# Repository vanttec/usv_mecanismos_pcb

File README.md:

# usv_mecanismos_pcb
PCB de Mecanismos
* STM32L431RTC
* Puente H (2) (6A maximo consumo, diseñar a 12A o 9A supongo)
* Drivers p/steppers (2)
* Conectores de seguridad (Molex?)
* CAN (MAX330 transcievers?) (1)
* Level Shifters (3.3V a 5V) (no se cuantos)

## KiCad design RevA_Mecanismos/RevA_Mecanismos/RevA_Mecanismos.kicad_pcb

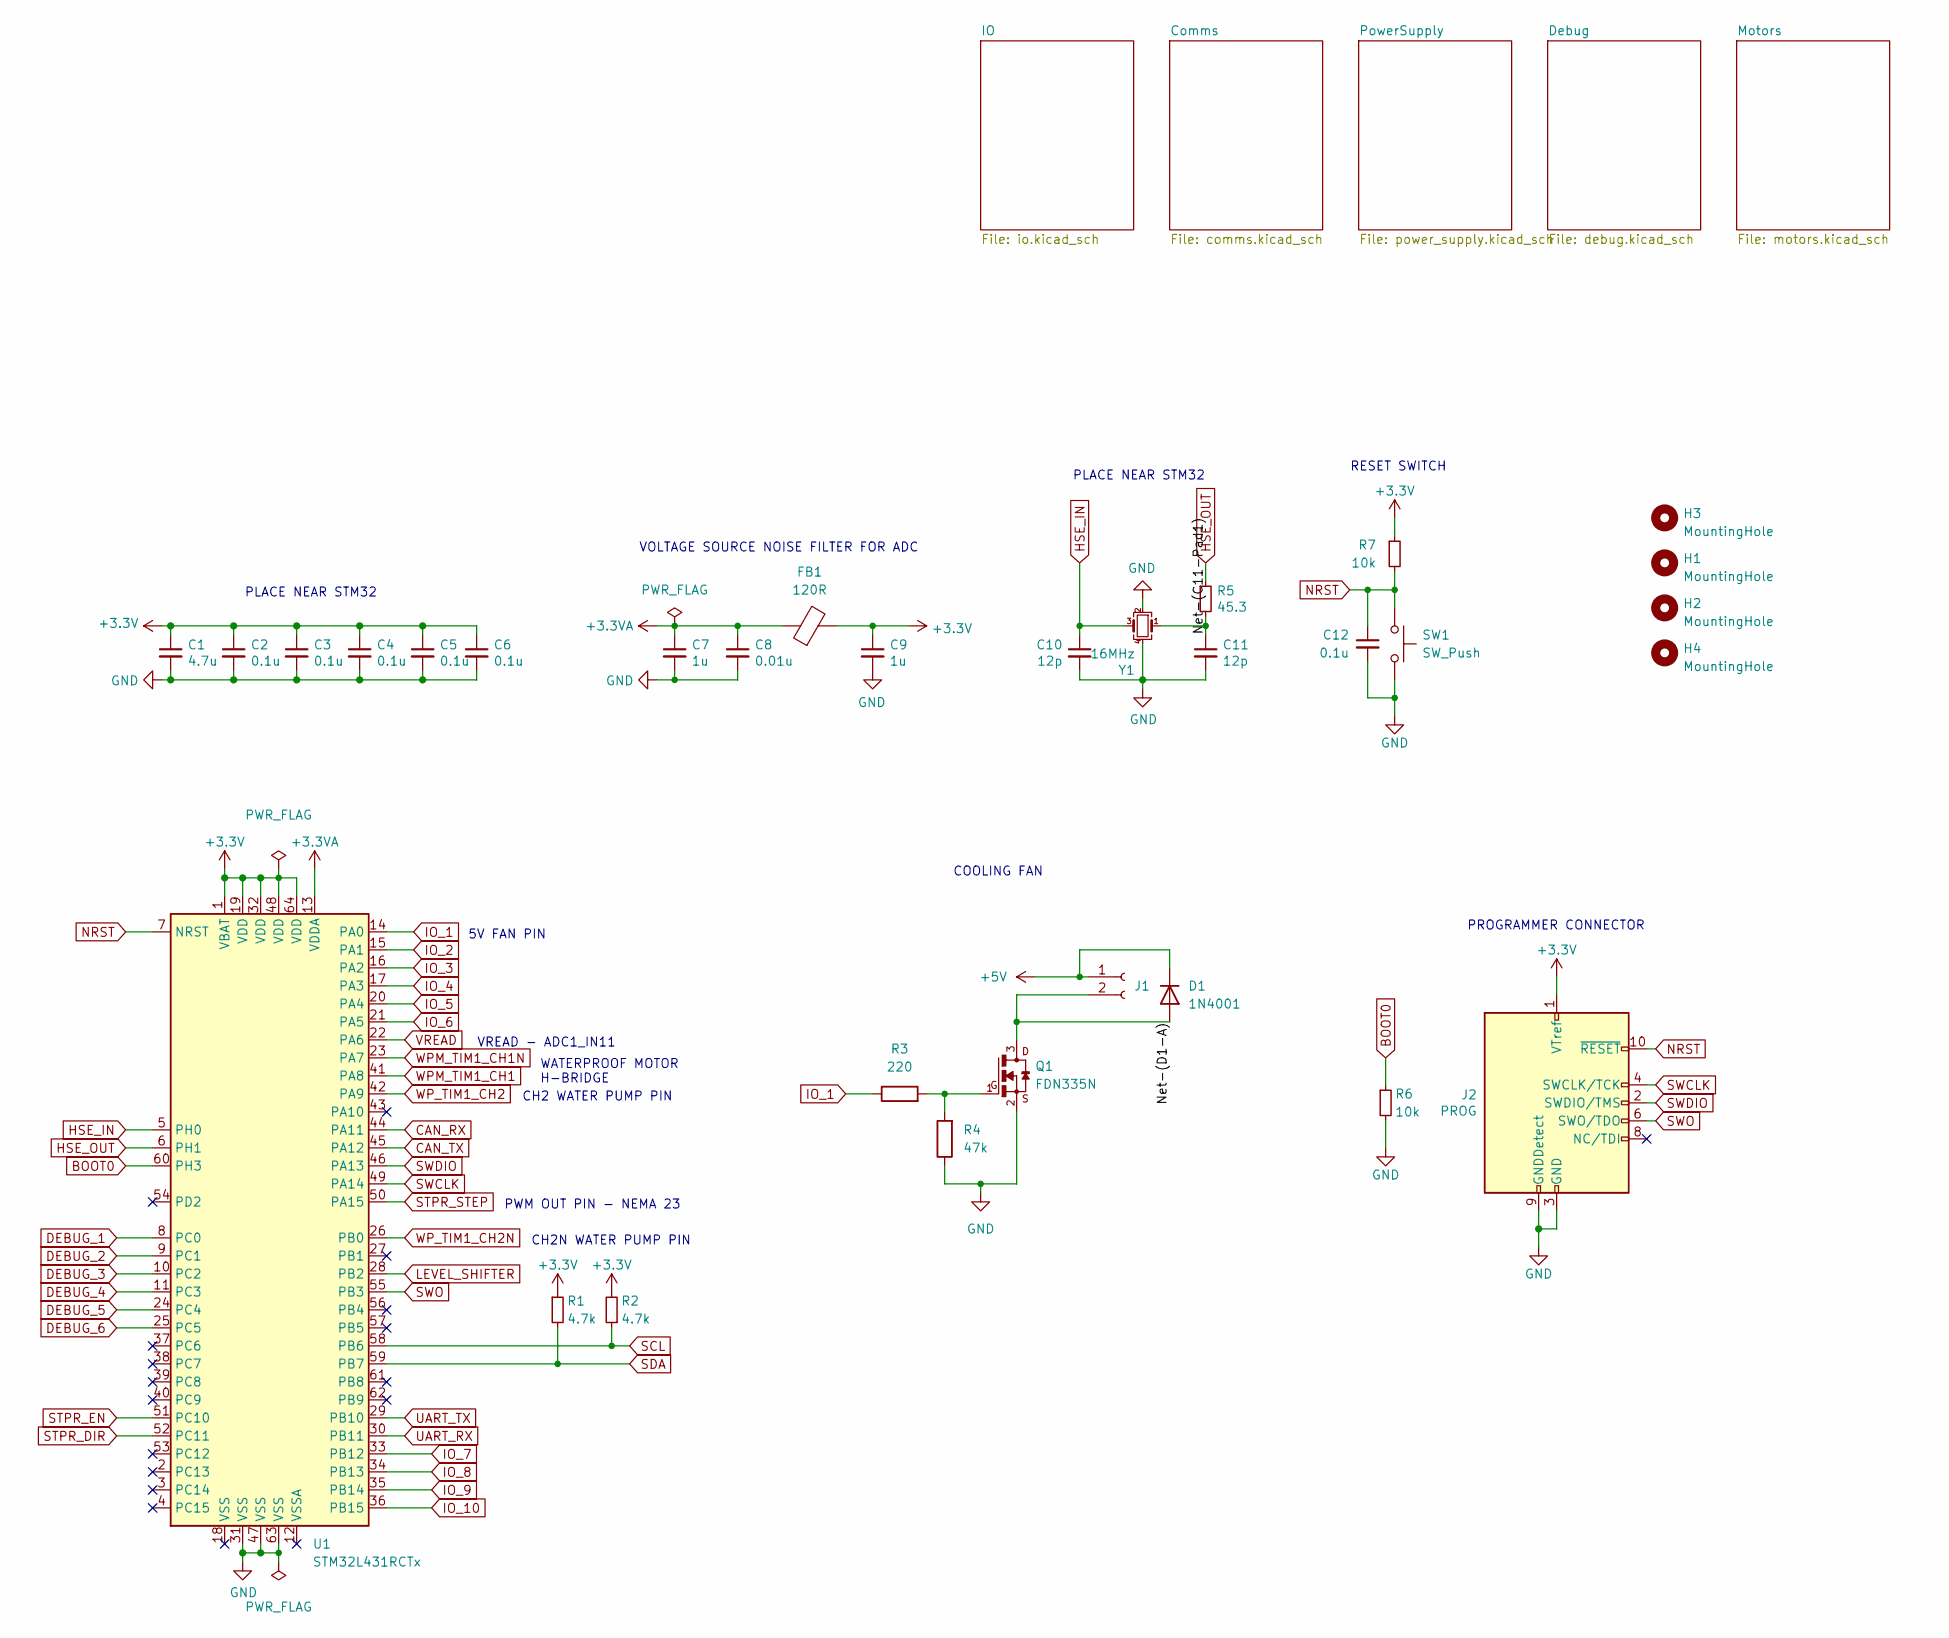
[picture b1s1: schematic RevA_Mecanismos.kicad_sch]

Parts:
C1: 4.7u; C_0603_1608Metric; PartNumber C0603C104K4RECTU; LCSC C165952
C2, C3, C4, C5, C6, C12: 0.1u; C_0603_1608Metric; PartNumber C0603C104K4RECTU; LCSC C165952
C7, C9: 1u; C_0603_1608Metric; PartNumber C0603C104K4RECTU; LCSC C165952
C8: 0.01u; C_0603_1608Metric; PartNumber C0603C104K4RECTU; LCSC C165952
C10, C11: 12p; C_0603_1608Metric; PartNumber C0603C120K5HACTU; LCSC C38523
D1: 1N4001; D_DO-41_SOD81_P10.16mm_Horizontal
FB1: 120R; L_0603_1608Metric
H1, H2, H3, H4: MountingHole; MountingHole_2.7mm_M2.5_DIN965_Pad
J1: Conn_01x02_Pin; PinHeader_1x02_P2.54mm_Vertical
J2: PROG; PinHeader_2x05_P1.27mm_Vertical; PartNumber 62201021121
Q1: FDN335N; SSOT-3; DigiKey_Part_Number FDN335NTR-ND
R1, R2: 4.7k; R_0603_1608Metric
R3: 220; R_0603_1608Metric
R4: 47k; R_0603_1608Metric
R5: 45.3; R_0603_1608Metric; PartNumber CRCW060347R0JNEAC; LCSC C23182
R6: 10k; R_0603_1608Metric
R7: 10k; R_0603_1608Metric; PartNumber CRCW06030000Z0EBC; LCSC C101250
SW1: SW_Push; SW_SPST_TL3305A
U1: STM32L431RCTx; LQFP-64_10x10mm_P0.5mm
Y1: 16MHz; Crystal_SMD_3225-4Pin_3.2x2.5mm; PartNumber ECS-160-12-33-AGN-TR; LCSC C13738

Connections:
+3.3V: C1.1, C2.1, C3.1, C4.1, C5.1, C6.1, C9.1, FB1.2, J2.1 (VTref), R1.1, R2.2, R7.1, U1.1 (VBAT), U1.19 (VDD), U1.32 (VDD), U1.48 (VDD), U1.64 (VDD); also elsewhere on the board
+3.3VA: C7.1, C8.1, FB1.1, U1.13 (VDDA)
+5V: D1.1 (K), J1.1; also elsewhere on the board
/Net-(C11-Pad1): C11.1, R5.2, Y1.1
/Net-(D1-A): D1.2 (A), J1.2, Q1.3
BOOT0: R6.1, U1.60 (PH3)
CAN_RX: U1.44 (PA11); also elsewhere on the board
CAN_TX: U1.45 (PA12); also elsewhere on the board
DEBUG_1: U1.8 (PC0); also elsewhere on the board
DEBUG_2: U1.9 (PC1); also elsewhere on the board
DEBUG_3: U1.10 (PC2); also elsewhere on the board
DEBUG_4: U1.11 (PC3); also elsewhere on the board
DEBUG_5: U1.24 (PC4); also elsewhere on the board
DEBUG_6: U1.25 (PC5); also elsewhere on the board
GND: C1.2, C2.2, C3.2, C4.2, C5.2, C6.2, C7.2, C8.2, C9.2, C10.2, C11.2, C12.2, J2.3 (GND), J2.5 (GND), J2.9 (GNDDetect), Q1.2, R4.1, R6.2, SW1.2, U1.31 (VSS), U1.47 (VSS), U1.63 (VSS), Y1.2, Y1.4; also elsewhere on the board
HSE_IN: C10.1, U1.5 (PH0), Y1.3
HSE_OUT: R5.1, U1.6 (PH1)
IO_1: R3.1, U1.14 (PA0)
IO_2: U1.15 (PA1); also elsewhere on the board
IO_3: U1.16 (PA2); also elsewhere on the board
IO_4: U1.17 (PA3); also elsewhere on the board
IO_5: U1.20 (PA4); also elsewhere on the board
IO_6: U1.21 (PA5); also elsewhere on the board
IO_7: U1.33 (PB12); also elsewhere on the board
IO_8: U1.34 (PB13); also elsewhere on the board
IO_9: U1.35 (PB14); also elsewhere on the board
IO_10: U1.36 (PB15); also elsewhere on the board
LEVEL_SHIFTER: U1.28 (PB2); also elsewhere on the board
NRST: C12.1, J2.10 (~RESET), R7.2, SW1.1, U1.7 (NRST)
unnamed: Q1.1, R3.2, R4.2
SCL: R2.1, U1.58 (PB6); also elsewhere on the board
SDA: R1.2, U1.59 (PB7); also elsewhere on the board
STPR_DIR: U1.52 (PC11); also elsewhere on the board
STPR_EN: U1.51 (PC10); also elsewhere on the board
STPR_STEP: U1.50 (PA15); also elsewhere on the board
SWCLK: J2.4 (SWCLK/TCK), U1.49 (PA14)
SWDIO: J2.2 (SWDIO/TMS), U1.46 (PA13)
SWO: J2.6 (SWO/TDO), U1.55 (PB3)
UART_RX: U1.30 (PB11); also elsewhere on the board
UART_TX: U1.29 (PB10); also elsewhere on the board
VREAD: U1.22 (PA6); also elsewhere on the board
WPM_TIM1_CH1: U1.41 (PA8); also elsewhere on the board
WPM_TIM1_CH1N: U1.23 (PA7); also elsewhere on the board
WP_TIM1_CH2: U1.42 (PA9); also elsewhere on the board
WP_TIM1_CH2N: U1.26 (PB0); also elsewhere on the board

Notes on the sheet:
5V FAN PIN
RESET SWITCH
VOLTAGE SOURCE NOISE FILTER FOR ADC
CH2N WATER PUMP PIN
VREAD - ADC1_IN11
COOLING FAN
PLACE NEAR STM32
PROGRAMMER CONNECTOR
PWM OUT PIN - NEMA 23
CH2 WATER PUMP PIN
WATERPROOF MOTOR H-BRIDGE

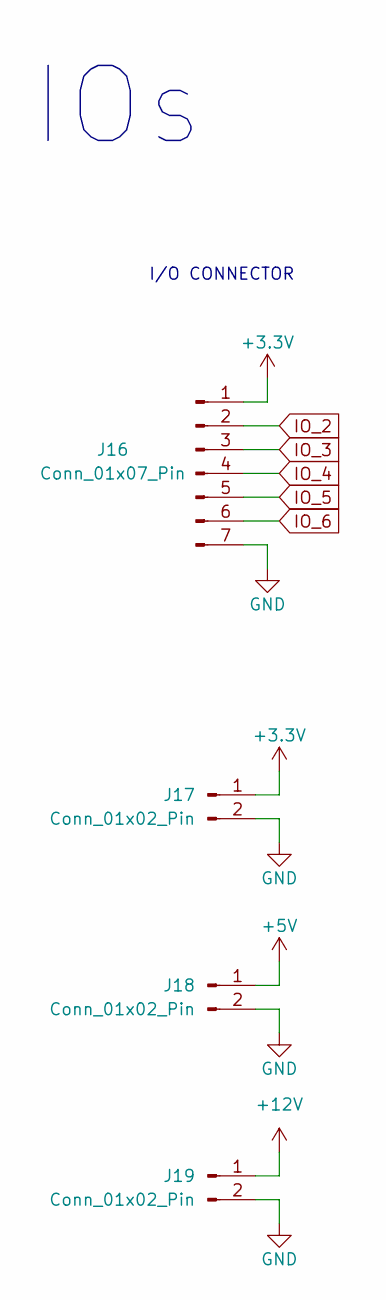
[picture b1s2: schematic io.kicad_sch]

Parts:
J16: Conn_01x07_Pin; PinHeader_1x02_P2.54mm_Vertical
J17: Conn_01x02_Pin; PinHeader_1x02_P2.54mm_Vertical
J18, J19: Conn_01x02_Pin; PinHeader_1x04_P2.54mm_Vertical

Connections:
+3.3V: J16.1, J17.1; also elsewhere on the board
+5V: J18.1; also elsewhere on the board
+12V: J19.1; also elsewhere on the board
GND: J16.7, J17.2, J18.2, J19.2; also elsewhere on the board
IO_2: J16.2; also elsewhere on the board
IO_3: J16.3; also elsewhere on the board
IO_4: J16.4; also elsewhere on the board
IO_5: J16.5; also elsewhere on the board
IO_6: J16.6; also elsewhere on the board

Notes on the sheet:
I/O CONNECTOR
IOs

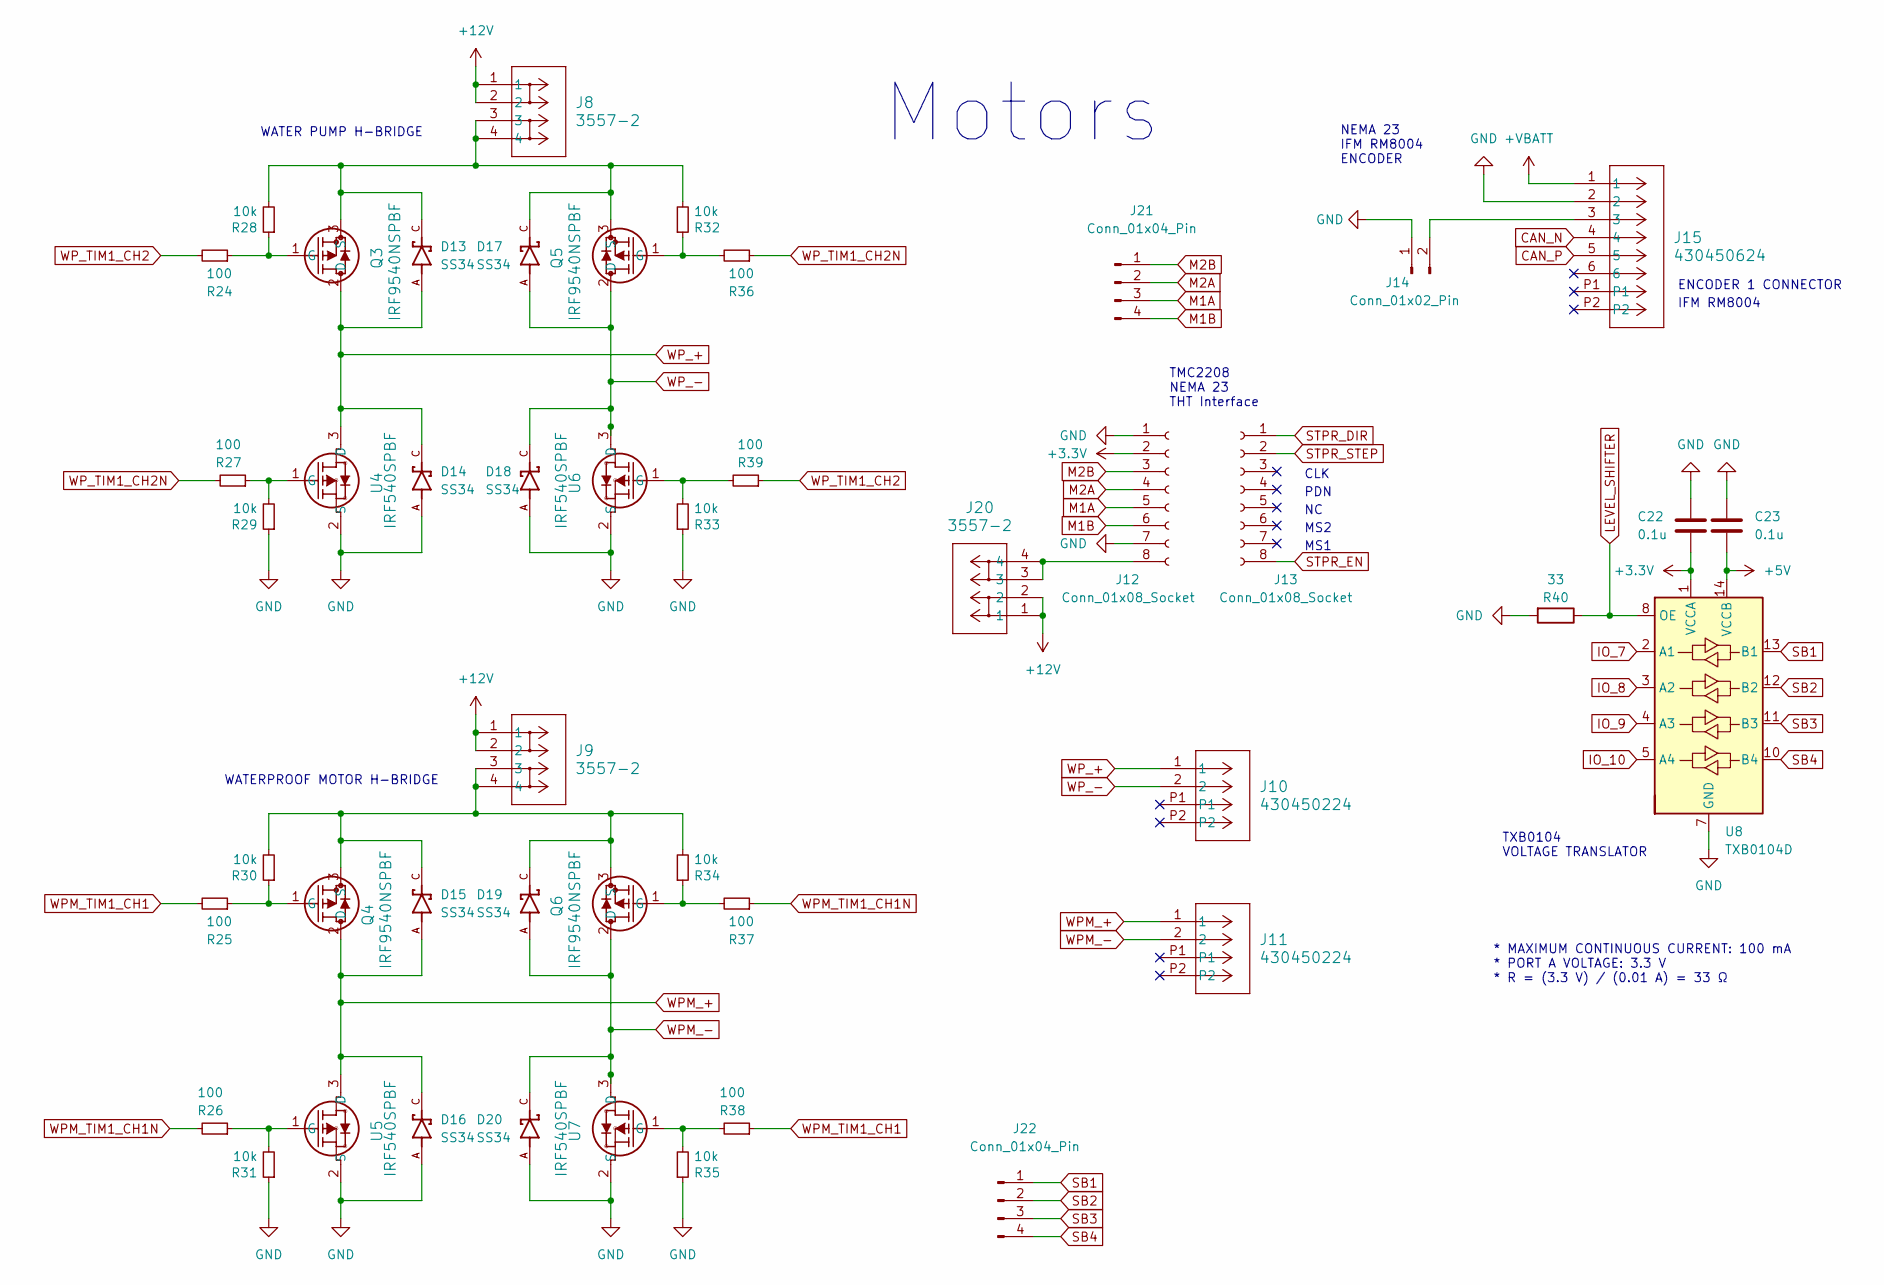
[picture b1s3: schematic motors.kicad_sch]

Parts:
C22, C23: 0.1u; C_0603_1608Metric
D13, D14, D15, D16, D17, D18, D20: SS34; DIOM7959X265N; PARTREV 31 Aug 2016
D19: SS34; PARTREV 31 Aug 2016
J8, J9: 3557-2; CONN_3557-2_KEY
J10, J11: 430450224; CON_430450224_MOL
J12: Conn_01x08_Socket; PinSocket_1x08_P2.54mm_Vertical
J13: Conn_01x08_Socket; CON_430450624_MOL
J14: Conn_01x02_Pin; PinHeader_1x07_P2.54mm_Vertical
J15: 430450624; PinHeader_1x02_P2.54mm_Vertical
J20: 3557-2; TerminalBlock_Altech_AK300-2_P5.00mm
J21, J22: Conn_01x04_Pin; PinHeader_1x04_P2.54mm_Vertical
Q3, Q4, Q5, Q6: IRF9540NSPBF; PMOSGDS_D2PAK_INF
R24, R25, R26, R27, R36, R37, R38, R39: 100; R_0603_1608Metric; PartNumber RGT1608P-821-B-T5; LCSC C101202
R28, R29, R30, R31, R32, R33, R34, R35: 10k; R_0603_1608Metric; PartNumber RGT1608P-821-B-T5; LCSC C101202
R40: 33; R_0603_1608Metric
U4, U5, U6, U7: IRF540SPBF; D2PAK_VIS
U8: TXB0104D; SOIC-14_3.9x8.7mm_P1.27mm

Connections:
+3.3V: C22.2, J12.2, U8.1 (VCCA); also elsewhere on the board
+5V: C23.2, U8.14 (VCCB); also elsewhere on the board
+12V: J8.1, J8.2, J9.1, J9.2, J20.1, J20.2; also elsewhere on the board
+VMOT: J15.1; also elsewhere on the board
CAN_N: J15.4; also elsewhere on the board
CAN_P: J15.5; also elsewhere on the board
GND: C22.1, C23.1, D14.A, D16.A, D18.A, D20.A, J12.1, J12.7, J14.1, J15.2, R29.1, R31.1, R33.1, R35.1, R40.2, U4.2 (S), U5.2 (S), U6.2 (S), U7.2 (S), U8.7 (GND); also elsewhere on the board
IO_7: U8.2 (A1); also elsewhere on the board
IO_8: U8.3 (A2); also elsewhere on the board
IO_9: U8.4 (A3); also elsewhere on the board
IO_10: U8.5 (A4); also elsewhere on the board
LEVEL_SHIFTER: R40.1, U8.8 (OE); also elsewhere on the board
M1A: J12.5, J21.3
M1B: J12.6, J21.4
M2A: J12.4, J21.2
M2B: J12.3, J21.1
unnamed: J12.8, J20.3, J20.4
unnamed: J14.2, J15.3
unnamed: Q3.1 (G), R24.1, R28.1
unnamed: D13.C, D17.C, J8.3, J8.4, Q3.3 (S), Q5.3 (S), R28.2, R32.2
unnamed: Q4.1 (G), R25.1, R30.1
unnamed: D15.C, D19.C, J9.3, J9.4, Q4.3 (S), Q6.3 (S), R30.2, R34.2
unnamed: Q5.1 (G), R32.1, R36.2
unnamed: Q6.1 (G), R34.1, R37.2
unnamed: R27.1, R29.2, U4.1 (G)
unnamed: R26.1, R31.2, U5.1 (G)
unnamed: R33.2, R39.2, U6.1 (G)
unnamed: R35.2, R38.2, U7.1 (G)
SB1: J22.1, U8.13 (B1)
SB2: J22.2, U8.12 (B2)
SB3: J22.3, U8.11 (B3)
SB4: J22.4, U8.10 (B4)
STPR_DIR: J13.1; also elsewhere on the board
STPR_EN: J13.8; also elsewhere on the board
STPR_STEP: J13.2; also elsewhere on the board
WPM_+: D15.A, D16.C, J11.1, Q4.2 (D), U5.3 (D)
WPM_-: D19.A, D20.C, J11.2, Q6.2 (D), U7.3 (D)
WPM_TIM1_CH1: R25.2, R38.1; also elsewhere on the board
WPM_TIM1_CH1N: R26.2, R37.1; also elsewhere on the board
WP_+: D13.A, D14.C, J10.1, Q3.2 (D), U4.3 (D)
WP_-: D17.A, D18.C, J10.2, Q5.2 (D), U6.3 (D)
WP_TIM1_CH2: R24.2, R39.1; also elsewhere on the board
WP_TIM1_CH2N: R27.2, R36.1; also elsewhere on the board

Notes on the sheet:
ENCODER 1 CONNECTOR
TXB0104 VOLTAGE TRANSLATOR
NEMA 23 IFM RM8004 ENCODER
IFM RM8004
TMC2208 NEMA 23 THT Interface
MS2
Motors
WATERPROOF MOTOR H-BRIDGE
* MAXIMUM CONTINUOUS CURRENT: 100 mA * PORT A VOLTAGE: 3.3 V * R = (3.3 V) / (0.01 A) = 33 Ω
CLK
PDN
MS1
WATER PUMP H-BRIDGE

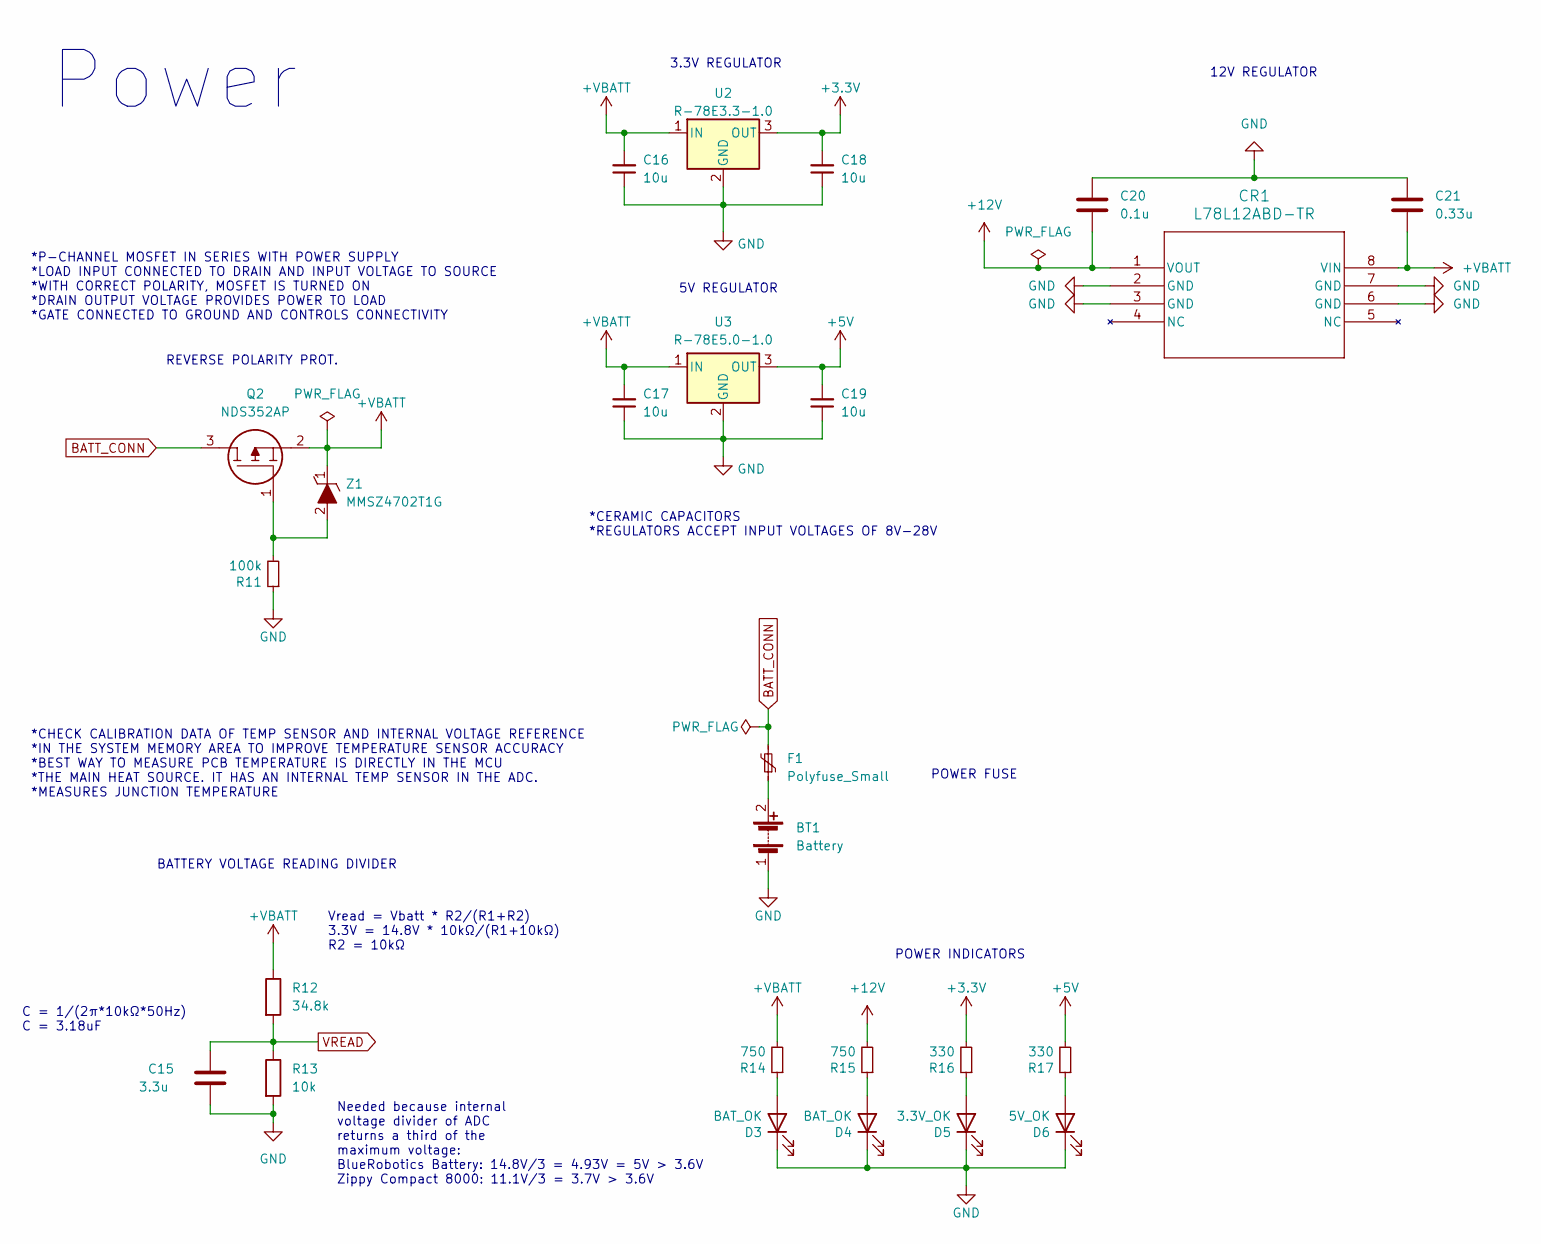
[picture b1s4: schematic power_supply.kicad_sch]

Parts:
BT1: Battery; AMASS_XT60-M_1x02_P7.20mm_Vertical
C15: 3.3u; C_0603_1608Metric
C16, C17, C18, C19: 10u; C_0603_1608Metric; LCSC C92487
C20: 0.1u; C_0603_1608Metric
C21: 0.33u; C_0603_1608Metric
CR1: L78L12ABD-TR; SO-8_STM
D3, D4: BAT_OK; LED_0603_1608Metric; PartNumber 150060RS75000; LCSC C181863
D5: 3.3V_OK; LED_0603_1608Metric; PartNumber 150060RS75000; LCSC C181863
D6: 5V_OK; LED_0603_1608Metric; PartNumber 150060RS75000; LCSC C181863
F1: Polyfuse_Small; Fuse_2920_7451Metric
Q2: NDS352AP; SOT95P237X111-3N; Manufacturer_Part_Number NDS352AP; Mouser Part Number 512-NDS352AP
R11: 100k; R_0603_1608Metric; PartNumber CRCW0603255KFKEAC; LCSC C328420
R12: 34.8k; R_0603_1608Metric
R13: 10k; R_0603_1608Metric
R14, R15: 750; R_0603_1608Metric; PartNumber RGT1608P-821-B-T5; LCSC C101202
R16, R17: 330; R_0603_1608Metric; PartNumber CRCW0603255KFKEAC; LCSC C328420
U2: R-78E3.3-1.0; Converter_DCDC_RECOM_R-78E-0.5_THT
U3: R-78E5.0-1.0; Converter_DCDC_RECOM_R-78E-0.5_THT
Z1: MMSZ4702T1G; SOD3716X135N; Manufacturer_Part_Number MMSZ4702T1G; Mouser Part Number 863-MMSZ4702T1G

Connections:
+3.3V: C18.2, R16.2, U2.3 (OUT); also elsewhere on the board
+5V: C19.2, R17.2, U3.3 (OUT); also elsewhere on the board
+12V: C20.2, CR1.1 (VOUT), R15.2; also elsewhere on the board
+VMOT: C16.2, C17.2, C21.2, CR1.8 (VIN), Q2.2, R12.1, R14.2, U2.1 (IN), U3.1 (IN), Z1.1; also elsewhere on the board
BATT_CONN: F1.2, Q2.3
GND: BT1.1 (-), C15.2, C16.1, C17.1, C18.1, C19.1, C20.1, C21.1, CR1.2 (GND), CR1.3 (GND), CR1.6 (GND), CR1.7 (GND), D3.1 (K), D4.1 (K), D5.1 (K), D6.1 (K), R11.1, R13.2, U2.2 (GND), U3.2 (GND); also elsewhere on the board
unnamed: BT1.2 (+), F1.1
unnamed: D3.2 (A), R14.1
unnamed: D4.2 (A), R15.1
unnamed: D5.2 (A), R16.1
unnamed: D6.2 (A), R17.1
unnamed: Q2.1, R11.2, Z1.2
VREAD: C15.1, R12.2, R13.1; also elsewhere on the board

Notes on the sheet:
12V REGULATOR
C = 1/(2π*10kΩ*50Hz) C = 3.18uF
*CHECK CALIBRATION DATA OF TEMP SENSOR AND INTERNAL VOLTAGE REFERENCE *IN THE SYSTEM MEMORY AREA TO IMPROVE TEMPERATURE SENSOR ACCURACY *BEST WAY TO MEASURE PCB TEMPERATURE IS DIRECTLY IN THE MCU *THE MAIN HEAT SOURCE. IT HAS AN INTERNAL TEMP SENSOR IN THE ADC. *MEASURES JUNCTION TEMPERATURE
5V REGULATOR
3.3V REGULATOR
*CERAMIC CAPACITORS *REGULATORS ACCEPT INPUT VOLTAGES OF 8V-28V
REVERSE POLARITY PROT.
Vread = Vbatt * R2/(R1+R2) 3.3V = 14.8V * 10kΩ/(R1+10kΩ) R2 = 10kΩ
BATTERY VOLTAGE READING DIVIDER
POWER FUSE
Power
*P-CHANNEL MOSFET IN SERIES WITH POWER SUPPLY *LOAD INPUT CONNECTED TO DRAIN AND INPUT VOLTAGE TO SOURCE *WITH CORRECT POLARITY, MOSFET IS TURNED ON *DRAIN OUTPUT VOLTAGE PROVIDES POWER TO LOAD *GATE CONNECTED TO GROUND AND CONTROLS CONNECTIVITY
POWER INDICATORS
Needed because internal voltage divider of ADC returns a third of the maximum voltage: BlueRobotics Battery: 14.8V/3 = 4.93V = 5V > 3.6V Zippy Compact 8000: 11.1V/3 = 3.7V > 3.6V

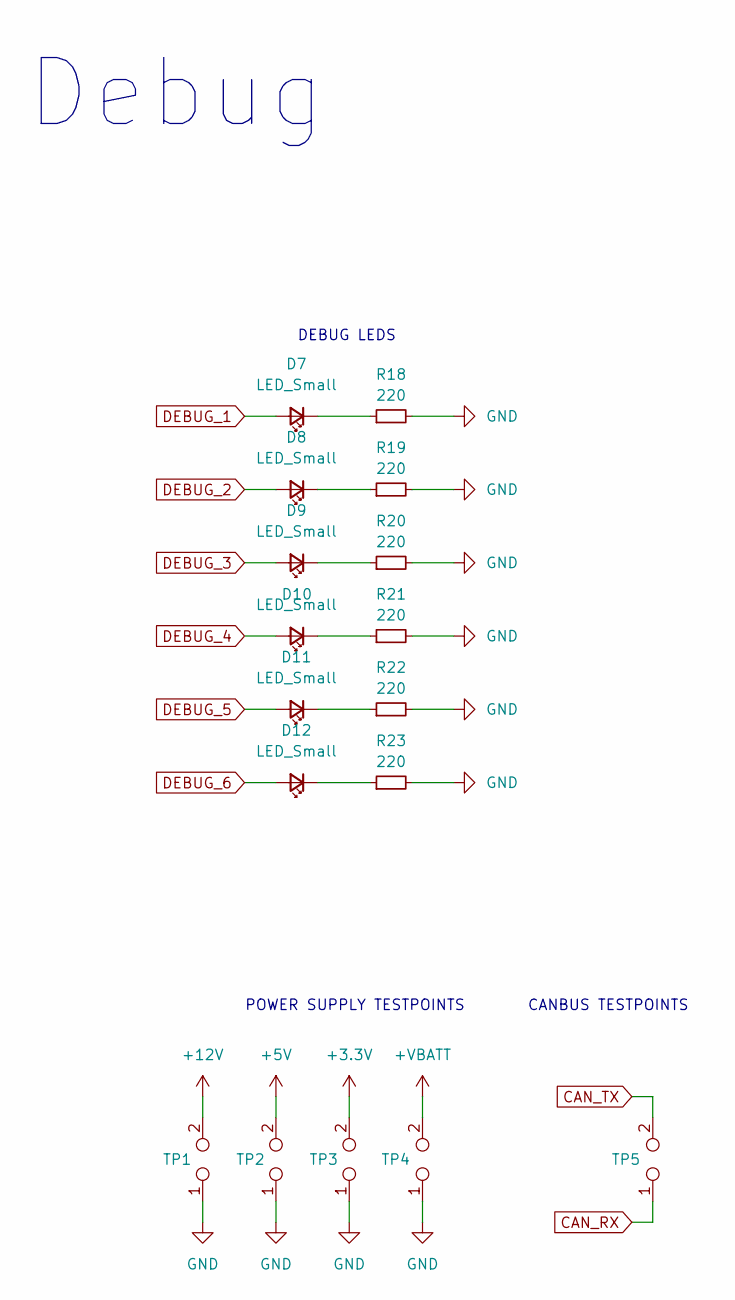
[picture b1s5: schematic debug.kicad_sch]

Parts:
D7, D8, D9, D10, D11, D12: LED_Small; LED_0603_1608Metric
R18, R19, R20, R21, R22, R23: 220; R_0603_1608Metric
TP1, TP2, TP3, TP4, TP5: TestPoint_2Pole; TestPoint_2Pads_Pitch5.08mm_Drill1.3mm

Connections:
+3.3V: TP3.2; also elsewhere on the board
+5V: TP2.2; also elsewhere on the board
+12V: TP1.2; also elsewhere on the board
+VMOT: TP4.2; also elsewhere on the board
CAN_RX: TP5.1; also elsewhere on the board
CAN_TX: TP5.2; also elsewhere on the board
DEBUG_1: D7.2 (A); also elsewhere on the board
DEBUG_2: D8.2 (A); also elsewhere on the board
DEBUG_3: D9.2 (A); also elsewhere on the board
DEBUG_4: D10.2 (A); also elsewhere on the board
DEBUG_5: D11.2 (A); also elsewhere on the board
DEBUG_6: D12.2 (A); also elsewhere on the board
GND: R18.2, R19.2, R20.2, R21.2, R22.2, R23.2, TP1.1, TP2.1, TP3.1, TP4.1; also elsewhere on the board
unnamed: D7.1 (K), R18.1
unnamed: D8.1 (K), R19.1
unnamed: D9.1 (K), R20.1
unnamed: D10.1 (K), R21.1
unnamed: D11.1 (K), R22.1
unnamed: D12.1 (K), R23.1

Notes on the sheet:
DEBUG LEDS
CANBUS TESTPOINTS
POWER SUPPLY TESTPOINTS
Debug

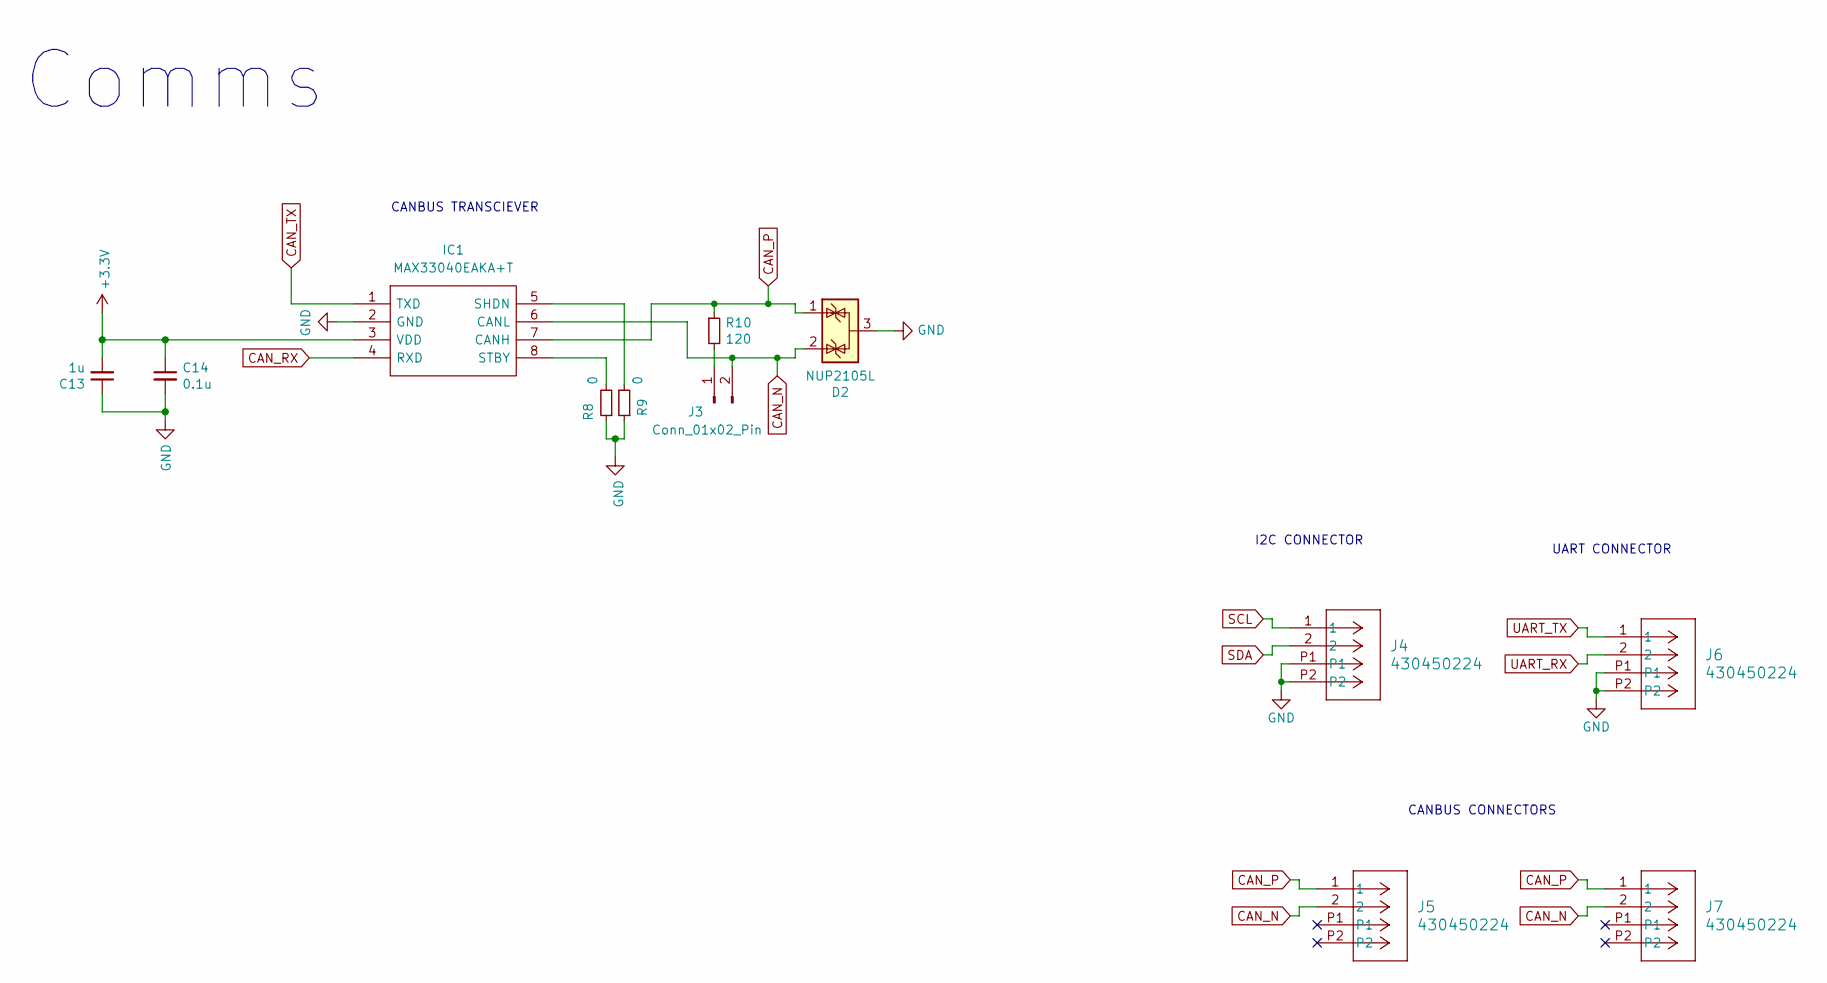
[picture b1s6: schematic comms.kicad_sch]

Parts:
C13: 1u; C_0603_1608Metric; LCSC C92828
C14: 0.1u; C_0603_1608Metric; LCSC C165952
D2: NUP2105L; SOT-23; PartNumber SZNUP2105LT3G; LCSC C284104
IC1: MAX33040EAKA+T; SOT65P280X145-8N; Manufacturer_Part_Number MAX33040EAKA+T; LCSC C5221297
J3: Conn_01x02_Pin; PinHeader_1x02_P1.27mm_Vertical
J4, J5, J6, J7: 430450224; CON_430450224_MOL
R8, R9: 0; R_0603_1608Metric; PartNumber CRCW06030000Z0EBC; LCSC C101250
R10: 120; R_0603_1608Metric; LCSC C114640

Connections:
+3.3V: C13.2, C14.1, IC1.3 (VDD); also elsewhere on the board
CAN_N: D2.2 (K), IC1.6 (CANL), J3.2, J5.2, J7.2; also elsewhere on the board
CAN_P: D2.1 (K), IC1.7 (CANH), J5.1, J7.1, R10.1; also elsewhere on the board
CAN_RX: IC1.4 (RXD); also elsewhere on the board
CAN_TX: IC1.1 (TXD); also elsewhere on the board
GND: C13.1, C14.2, D2.3 (A), IC1.2 (GND), J4.P1, J4.P2, J6.P1, J6.P2, R8.1, R9.1; also elsewhere on the board
unnamed: IC1.5 (SHDN), R9.2
unnamed: IC1.8 (STBY), R8.2
unnamed: J3.1, R10.2
SCL: J4.1; also elsewhere on the board
SDA: J4.2; also elsewhere on the board
UART_RX: J6.2; also elsewhere on the board
UART_TX: J6.1; also elsewhere on the board

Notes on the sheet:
UART CONNECTOR
I2C CONNECTOR
CANBUS TRANSCIEVER
CANBUS CONNECTORS
Comms

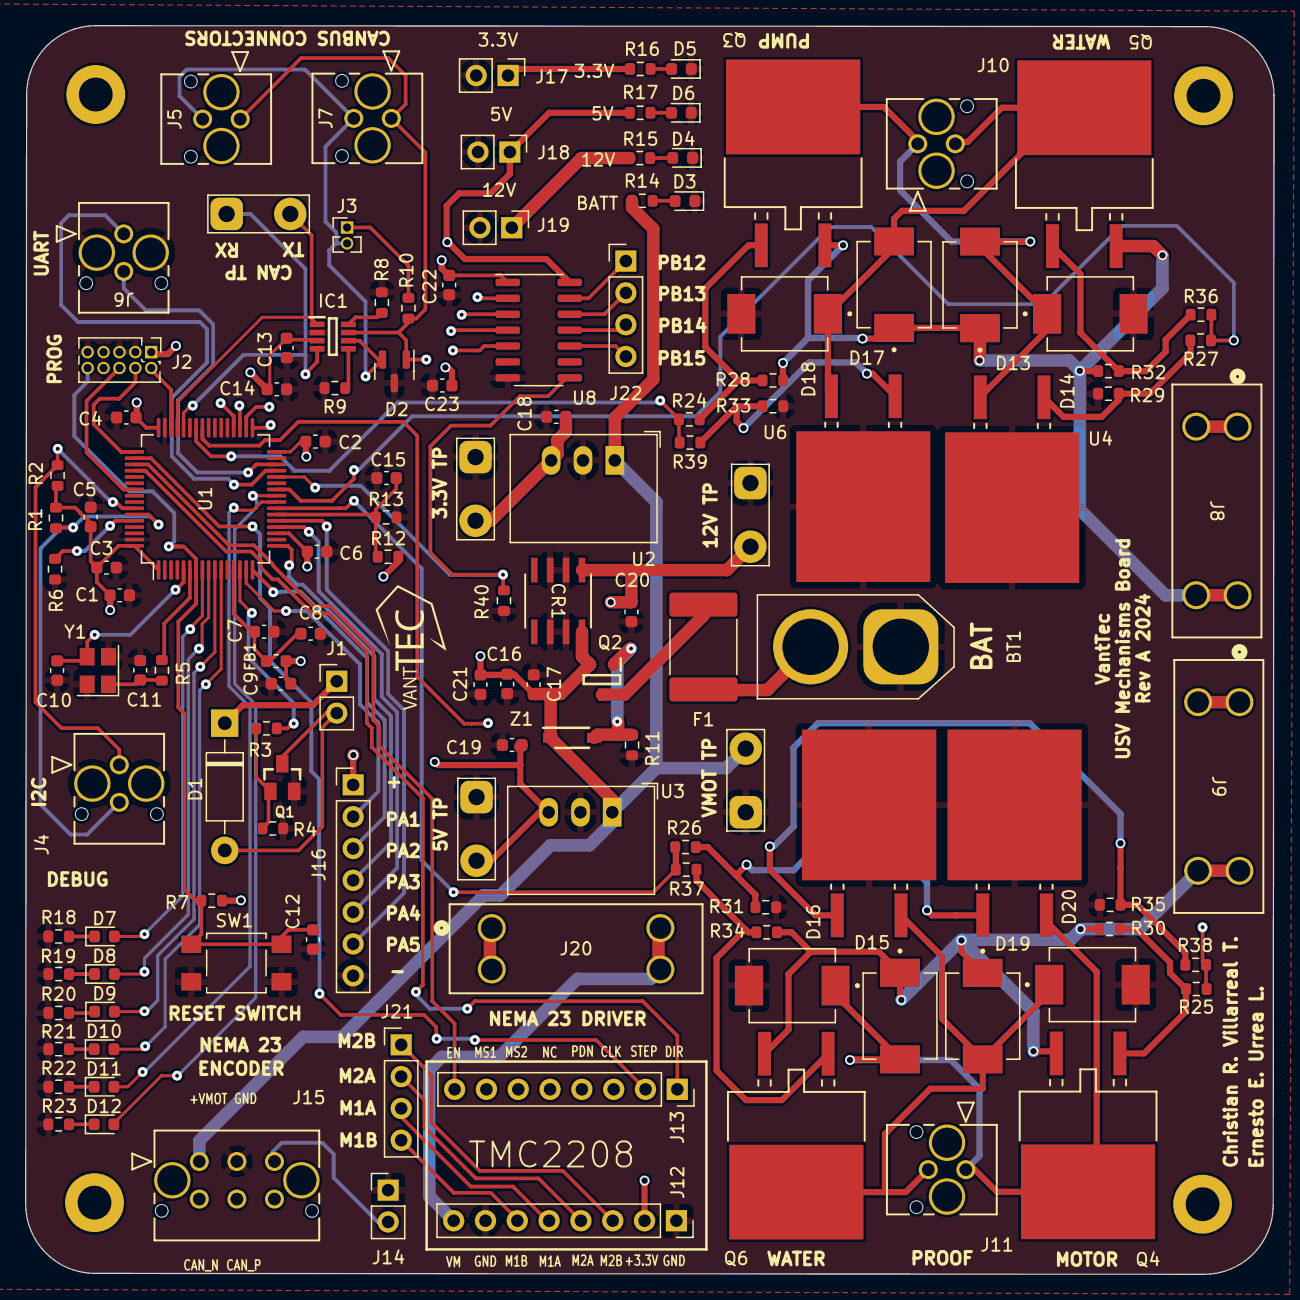
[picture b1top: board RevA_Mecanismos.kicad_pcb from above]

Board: 4 copper layers, 99.7 x 99.7 mm, 136 parts (0 on the bottom side), 89 nets.

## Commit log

2024-04-19 Created KiCad 7 Project
2024-04-19 Added component files for CAN Transcievers, Molex Connectors and STM32
2024-04-21 Added STM32 and initial subsystems: comms, power, debug, and motors
2024-04-24 Added H-Bridges and voltage regulators
2024-05-13 Created PCB project
2024-07-13 Adiciones a secciones de motores y power supply para placa de mecanismos
2024-07-15 Debug connectors and pwr flag to +12v
2024-07-26 Updated STM32 USV Mechanism PCB
2024-10-24 Complete schematic and pcb designs, routes missing and not yet complete
2024-10-24 Correction made to footprint for J3 pin header
2024-10-28 PCB Routing completed
2024-10-28 PCB Routing complete
2024-10-28 Correct sizes for power connections between VBATT/VMOT, +12V, +5V, and +3V made
2024-10-28 Corrections made to power supply routes and via sizes
2024-10-28 Name of developer added to PCB
2024-11-01 Replacement of screw terminals for molex connectors
2024-11-02 Corrections to component footprints in schematic design made during the development of BOM
2024-11-02 Placement and Gerber Files added
2024-11-02 PDF and former gerber files deleted in main directory
2024-11-02 ZIP file with Gerber and DRL files generated
